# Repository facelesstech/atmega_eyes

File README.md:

# atmega_eyes
2015 Halloween project with 8x8 led matrix, RGB LED and candle LED

Blog post - https://facelesstech.wordpress.com/2015/10/31/atmega_eyes-animated-eyes-for-pumpkin/

hardware video - https://www.youtube.com/watch?v=CcRrgkYMQW4

Pumpkin video - https://www.youtube.com/watch?v=LH3Dhd0DaJk

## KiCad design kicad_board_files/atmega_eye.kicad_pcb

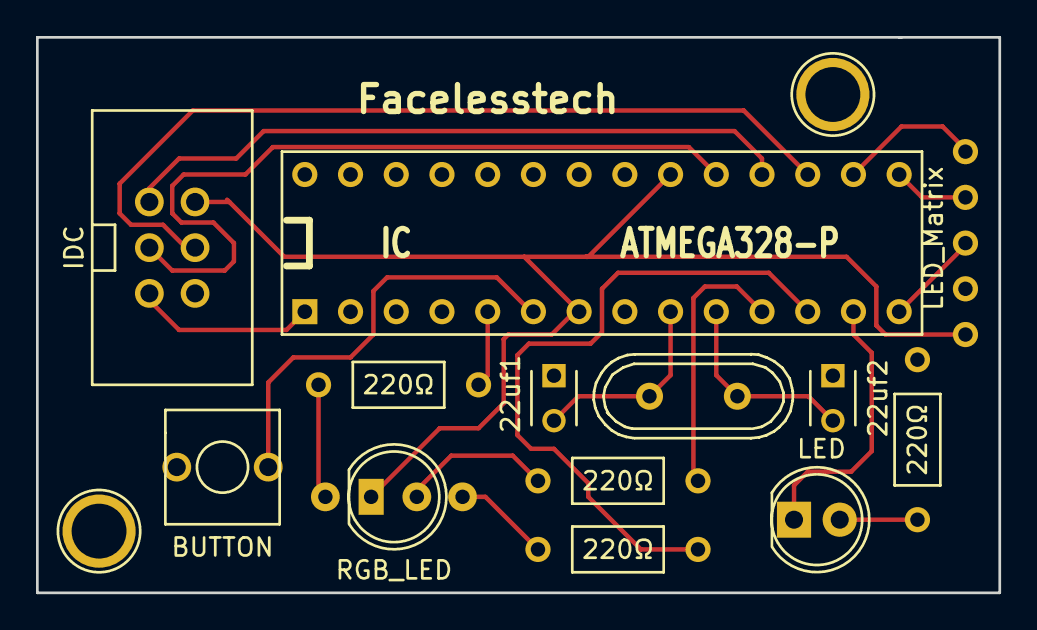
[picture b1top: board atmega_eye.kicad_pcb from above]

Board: 2 copper layers, 53.5 x 30.9 mm, 14 parts (0 on the bottom side), 20 nets.

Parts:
16Mhz: Crystal; Crystal_HC49-U_Vertical
22uf1, 22uf2: C; C_Disc_D3_P2.5
220Ω, 220Ω#2, 220Ω#3, 220Ω#4: R; Resistor_Horizontal_RM9mm
CON1: IDC; IDC_6pin_custom
D1: LED; LED-5MM
D2: RGB_LED; RGB_LED_custom
IC: ATMEGA328-P; atmega328_socket
SW1: BUTTON; 2PIN_BUTTON_custom
U1: LED_Matrix; LED_Matrix_custom
VAL: OSH_final_silks_back

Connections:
GND: 22uf1.1, 22uf2.1, 220Ω#4.1, CON1.6, IC.8, IC.22, SW1.2, U1.2
unnamed: 16Mhz.1, 22uf2.2, IC.10
unnamed: 16Mhz.2, 22uf1.2, IC.9
unnamed: 220Ω.1, D2.1
unnamed: 220Ω.2, IC.5
unnamed: 220Ω#2.1, D2.3
unnamed: 220Ω#2.2, IC.11
unnamed: 220Ω#3.1, D2.4
unnamed: 220Ω#3.2, IC.12
unnamed: 220Ω#4.2, D1.2
unnamed: CON1.1, IC.18
unnamed: CON1.3, IC.19
unnamed: CON1.4, IC.17
unnamed: CON1.5, IC.1
unnamed: D1.1, IC.13
unnamed: IC.6, SW1.1
unnamed: IC.14, U1.3
unnamed: IC.15, U1.4
unnamed: IC.16, U1.5
VCC: CON1.2, D2.2, IC.7, IC.20, U1.1

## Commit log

2015-09-21 First working build, just the basics all working
2015-09-22 updated the eyes and added button control to the rgb leds and candle led
2015-09-24 Gerber files created in kicad
2015-09-26 cycle though animations between eyes and hearts
2015-10-07 Added better eye animation and a few more bug fixes ;)
2015-10-13 added -std=gnu99 to the Makefile so the ATOMIC_BLOCK code will work
2015-10-13 Test code so you can test out your animation before adding into your main code
2015-10-29 changed it to eyes only and re-done the cycle code
2015-10-31 added links to blog and videos
2015-11-04 added rgb scroll code and refined the number of colours you can pick with the button
2016-09-24 Added board files
